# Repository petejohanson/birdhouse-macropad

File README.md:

# Birdhouse Macropad

**WIP: NOT FULLY ROUTED YET**

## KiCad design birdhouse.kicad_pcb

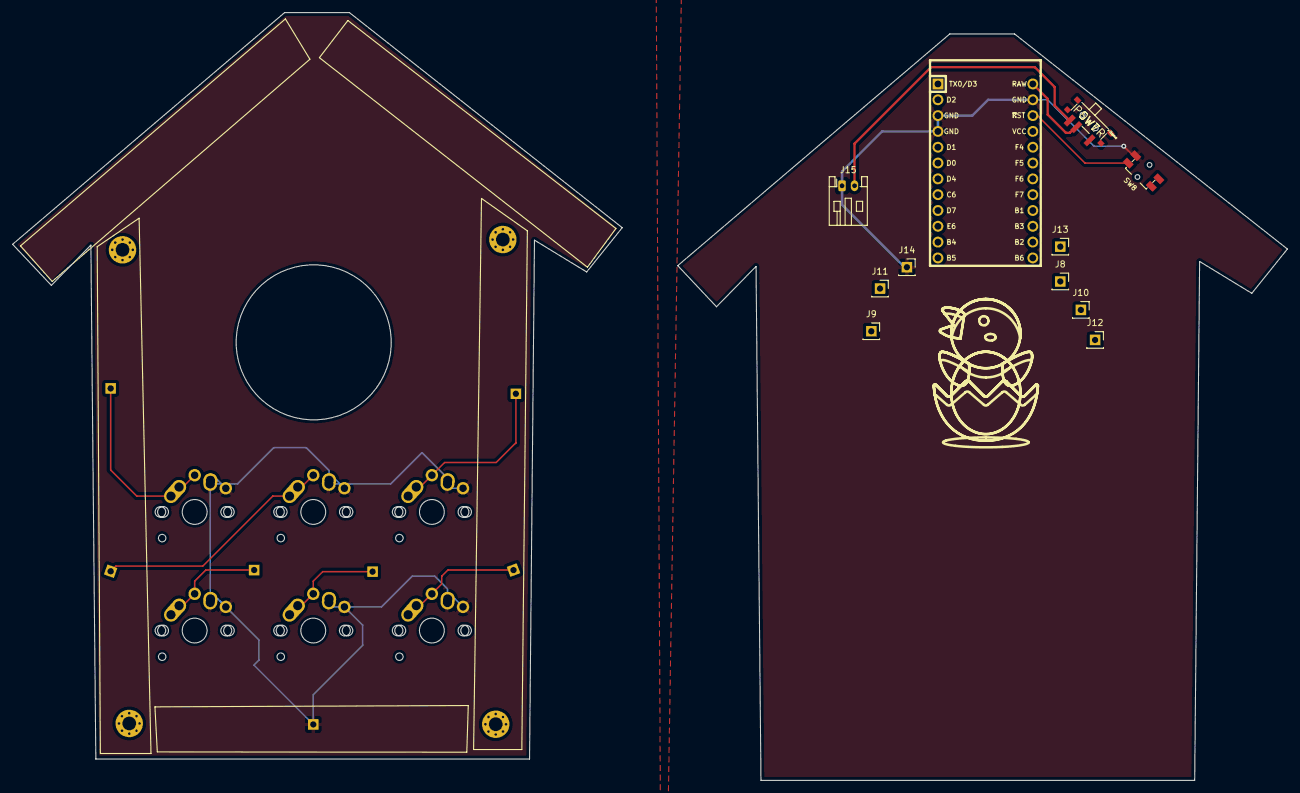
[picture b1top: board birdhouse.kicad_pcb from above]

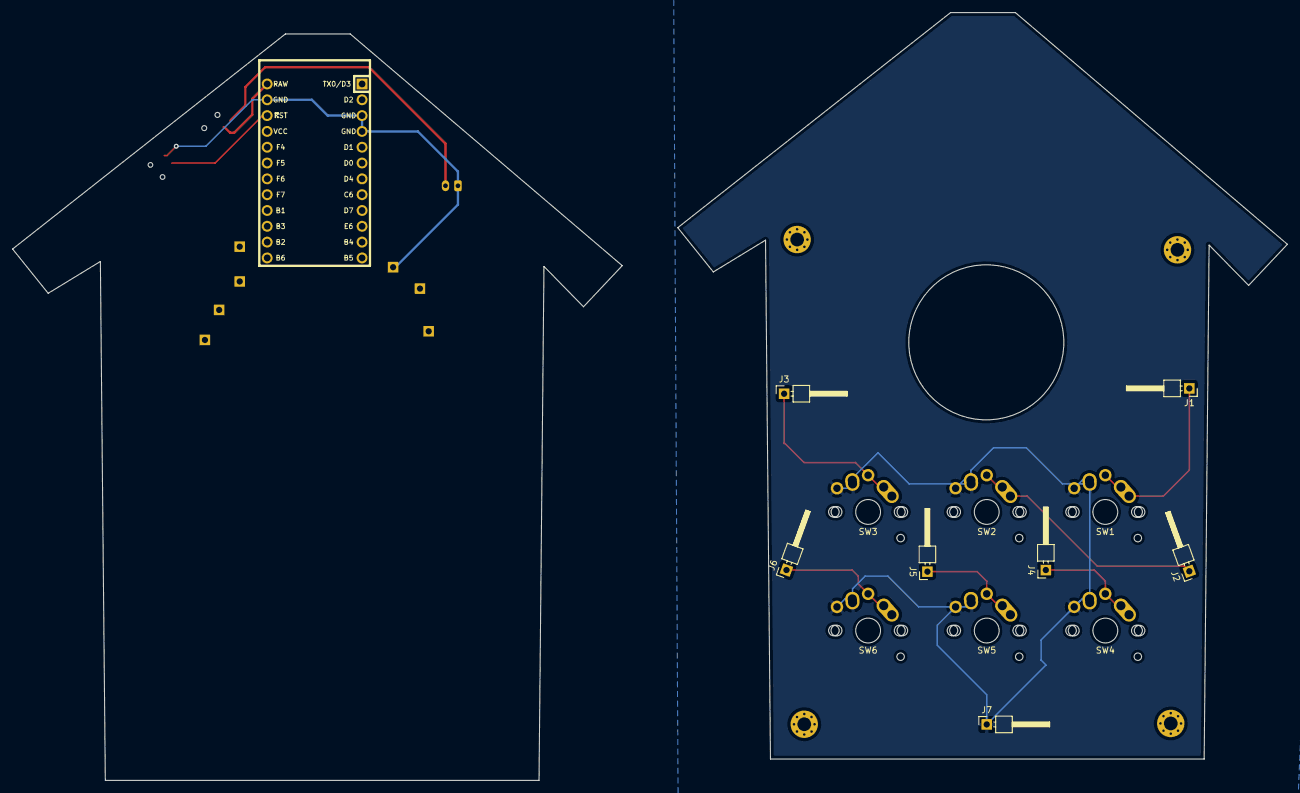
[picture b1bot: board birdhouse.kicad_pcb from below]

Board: 2 copper layers, 204.8 x 123.3 mm, 28 parts (7 on the bottom side), 11 nets.

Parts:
J1, J2, J3, J4, J5, J6, J7: Conn_01x01_Female; PinHeader_1x01_P2.54mm_Horizontal
J8: J1_BACK; PinSocket_1x01_P2.54mm_Vertical
J9: J2_BACK; PinSocket_1x01_P2.54mm_Vertical
J10: J3_BACK; PinSocket_1x01_P2.54mm_Vertical
J11: J4_BACK; PinSocket_1x01_P2.54mm_Vertical
J12: J5_BACK; PinSocket_1x01_P2.54mm_Vertical
J13: J6_BACK; PinSocket_1x01_P2.54mm_Vertical
J14: J7_BACK; PinSocket_1x01_P2.54mm_Vertical
J15: JST PH; JST_PH_S2B-PH-K_1x02_P2.00mm_Horizontal
SW1, SW2, SW3, SW4, SW5, SW6: SW_Push; MX-Alps-Choc-1U-NoLED
SW7: POWER; MSK-12C02
SW8: RESET; EVQPUC02K
U1: ProMicro; ArduinoProMicro
U4, U4#2, U4#3, U4#4: HOLE; MountingHole_2.2mm_M2_Pad_Via

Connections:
GND: J14.1, J15.1, SW8.2, U1.3, U1.4, U1.23
unnamed: J1.1, SW1.2
unnamed: J2.1, SW2.2
unnamed: J3.1, SW3.2
unnamed: J4.1, SW4.2
unnamed: J5.1, SW5.2
unnamed: J6.1, SW6.2
unnamed: J7.1, SW1.1, SW2.1, SW3.1, SW4.1, SW5.1, SW6.1
RAW: SW7.2, U1.24
RST: SW8.1, U1.22
VBAT: J15.2, SW7.1

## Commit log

2021-04-07 Initial (incomplete) birdhouse macropad.
2021-04-07 Initial README.
2021-04-07 Syntax fix for inline image.
